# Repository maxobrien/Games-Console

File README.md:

# Games Console Project - Max O'Brien

Above are all the files for my games console project.

## PCB Design Files
The PCB was originally designed in <a href="http://kicad.org/">KiCad 4.0.7</a> however other versions may still be able to open it. The board is a 2-layered design that can easily be manufactured at most places if that is what you wish to do.

**UPDATE** As of KiCad version 5.0 the board can still be opened however, you will need to run the automatic schematic symbol converter.

## STL Files
These files are for the enclosure of the games console. They fit the PCB supplied and so would need to be changed if you changed the dimensions of the board. If you are making your own then they can just be printed on a normal 3D printer, however, I would suggest you choose settings, and material, that will yield the highest quality detail as some of the model contains fine details. I chose black and white (as seen in the above render) and also printed it in SLS nylon.

## The Code
The code is written in the Arduino IDE. This means to open it, you will need the <a href="https://www.arduino.cc/en/Main/Software">Arduino IDE</a>. Before loading the code onto the micro, you will first have to burn a bootloader. Some guides to do this are listed below, however, doing your own research may yield better results.

- https://www.arduino.cc/en/Hacking/Bootloader
- https://learn.adafruit.com/ftdi-friend/programming-the-arduino-bootloader
- http://www.gammon.com.au/breadboard

Once the bootloader has be burned, you can upload the code. To do this, ensure your programmer is connected with a USB cable and open up the code in the Arduino IDE. Also ensure that the programmer is correctly connected to the programming header (Bottom Left) on the PCB. Check that all 5 tabs can be seen along the top labelled; "Main", "Breakout", "Menu", "pong" and "Settings". Next go to 'Tools > Board' and ensure 'Arduino/Genuino Uno' is selected. Then go to 'Tools > Port' and select the right port for your programmer. Finally, select 'Sketch > Upload Using Programmer'. Once this operation is complete, you should have a working games console!

## Console Renders
<details>
  <summary>Click to show renders</summary>

</details>

## Required Libraries for Code
- U8g2

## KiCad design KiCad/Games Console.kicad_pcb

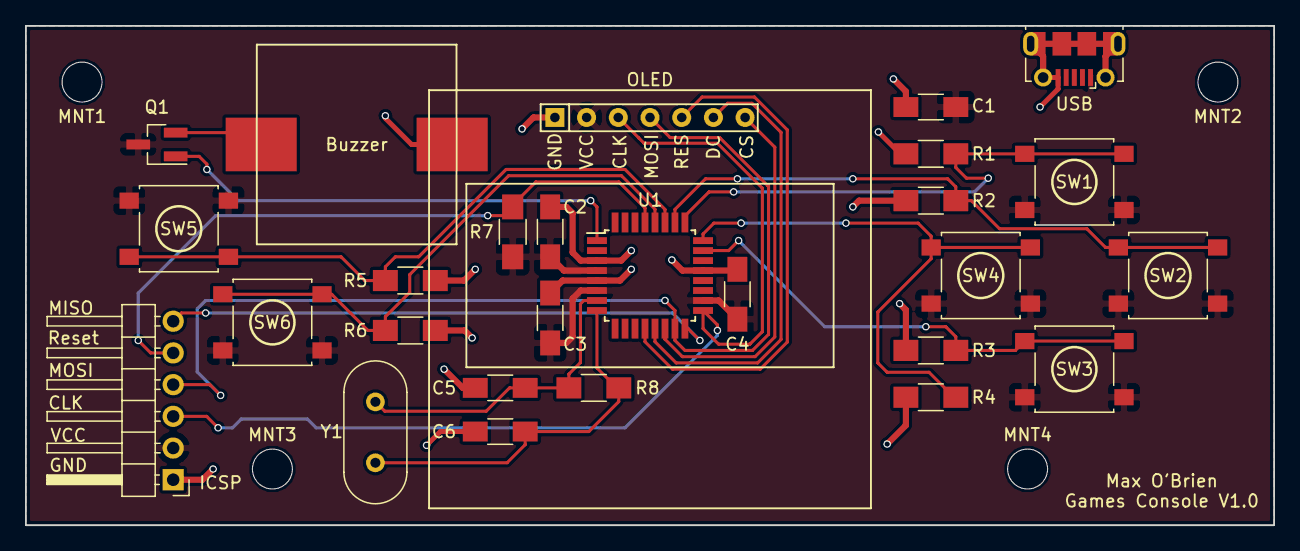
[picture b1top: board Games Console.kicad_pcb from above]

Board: 2 copper layers, 100.0 x 40.0 mm, 31 parts (0 on the bottom side), 19 nets.

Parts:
Buzzer: Buzzer; KMTG1603_Piezo_Buzzer
C1, C2, C3, C4: 0.1uF; C_1206_HandSoldering
C5, C6: 18pF; C_1206_HandSoldering
ICSP: Conn_01x06_Male; Pin_Header_Angled_1x06_Pitch2.54mm
MNT1, MNT2, MNT3, MNT4: MountingHole_3.2mm_M3
OLED: Conn_01x07_Male; OLED-1.3
Q1: 2N7002; SOT-23_Handsoldering
R1, R2, R3, R4, R5, R6, R7: 10k; R_1206_HandSoldering
R8: 1M; R_1206_HandSoldering
SW1, SW2, SW3, SW4, SW5, SW6: SW_Push; SW_SPST_B3S-1000
U1: ATMEGA328P-AU; TQFP-32_7x7mm_Pitch0.8mm
USB: USB_OTG; USB_Micro-B_Molex-105017-0001
Y1: 16mHz; Crystal_HC49-4H_Vertical

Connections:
+5V: C1.1, C2.1, C3.1, C4.1, ICSP.2, OLED.2, Q1.3, R7.2, SW1.1, SW2.1, SW3.1, SW4.1, SW5.1, SW6.1, U1.4, U1.6, U1.18, USB.1
BUZZER: Q1.1, U1.1
CLK: ICSP.3, OLED.3, U1.17
CS: OLED.7, U1.14
DC: OLED.6, U1.13
DOWN: R3.2, SW3.2, U1.23
GND: Buzzer.2, C1.2, C2.2, C3.2, C4.2, C5.1, C6.1, ICSP.1, OLED.1, R1.1, R2.1, R3.1, R4.1, R5.1, R6.1, U1.3, U1.5, U1.21, USB.5, USB.6
LEFT: R4.2, SW4.2, U1.24
MENU: R5.2, SW5.2, U1.27
MISO: ICSP.6, U1.16
MOSI: ICSP.4, OLED.4, U1.15
unnamed: Buzzer.1, Q1.2
unnamed: C5.2, R8.1, U1.7, Y1.1
unnamed: C6.2, R8.2, U1.8, Y1.2
unnamed: ICSP.5, R7.1, U1.29
RES: OLED.5, U1.12
RIGHT: R2.2, SW2.2, U1.26
SELECT: R6.2, SW6.2, U1.28
UP: R1.2, SW1.2, U1.25

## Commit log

2018-02-26 Added KiCad PCB files
2018-02-26 Added STL files for printing
2018-02-26 Added Arduino Code
2018-02-26 Added render images
2018-02-26 Added main information to README
2018-02-28 Updated title
2019-04-03 Added required libraries
2019-08-21 Added gerber files
2021-11-08 Update README.md
    https://forum.kicad.info/t/warning-avoid-all-links-to-kicad-pcb-org-use-kicad-org/31521
